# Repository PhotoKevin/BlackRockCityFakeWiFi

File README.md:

# BlackRockCityFakeWiFi

## Purpose
Create a joke WiFi access point for Black Rock City (aka Burning Man). The person trying to use the access point gets a huge list of Terms and Conditions in ever smaller font. Once they agree, they are run through some questions to "Prove they're not a robot".

Finally they get told that "Dorking around on the Internet" is against the principle of Immediacy and are dumped.

]
]
])

## Development Environment
I developed this on generic ESP8266 and ESP32 boards using the Arduino IDE. It also supports the OLED display on a Heltec WiFi Kit 32 (V3) or WiFi Kit 8. In addition to the OLED the Heltec boards are nice in that they can run off of either USB or a LiPo battery and can charge the battery from USB.

The web pages were created with the [Pulsar](https://pulsar-edit.dev) editor. A small C program is then used to convert the
pages into data stored in the main flash memory. The C program was developed in Visual Studio 2019.

Boards that I have tested on are:

- [Heltec WiFi Kit 32 (V3)](https://heltec.org/project/wifi-kit32-v3/)  
- [Heltec WiFi Kit 8](https://heltec.org/project/wifi-kit-8/)  
- [LOLIN (Wemos) D1 R1](https://www.wemos.cc/en/latest/d1/index.html)  
- [IdeaSpark ESP32](https://www.amazon.com/s?k=ideaspark)

## Captive Portal
The code implements a Captive Portal which operates like the typical free WiFi you'd find at a restaurant.
When the user connects it grabs all traffic from that user regardless of what they asked for and redirects it
to its signon process. I owe a lot to the [Mobile Rick Roll](https://github.com/idolpx/mobile-rr) project for their work in figuring out how to
implement this.

## Building the project
I'm using the Arduino 2.3.2 IDE.

- After installing the IDE go to the preferences (Control-Comma) and add these Additional Board Manager URLs.

- https://arduino.esp8266.com/stable/package_esp8266com_index.json  
- https://espressif.github.io/arduino-esp32/package_esp32_index.json
- https://github.com/Heltec-Aaron-Lee/WiFi_Kit_series/releases/download/3.0.0/package_heltec_esp32_index.json

- Exit and restart the IDE.

- In the Boards Manager (left column, second icon from the top) and install
    - "esp32 by Espressif Systems" version 3.0.1
    - "Arduino ESP32 Boards" version 2.0.13
    - "ESP8266 Boards" version 3.1.2

- Now go to the Library Manager (left column, third icon from the top) and install
    - ArduionJson by Benoit Blanchon. 7.0.4
    - ESP Async WebServer by me-no-dev 3.0.6
    - AsyncTCP by me-no-dev 3.1.4
    - ESPAsyncTCP by dvarrel 1.2.4
    - U8g2 by oliver. 2.34.22 - If using one of the boards with an OLED display.

- Plug your ESP board into a USB port.

- Click on the drop down in the button bar. Select your board and COM port.

- Lastly click on the Upload (right arrow) button to compile and install the software.

## Accessing the Status and Configuration Pages
- Bring up the list of access points and find BRC Open WiFi.
- Select that and you should be redirected to the giant page of legalese.
- Find the sentence "The following are representative examples only and do not comprise a comprehensive list of illegal</a> uses:"
- Click on the word "illegal".
- Log in with the default credentials of admin/changeme (both are all lower case).

]
]

## Configuration Options
- SSID - Name of the Access Point that shows up on your phone.
- Username - Username for accessing the statistics and settings.
- Password - Password for same. If left blank the previous password will remain in effect.
- IP Address - The IP Address for the Access Point. Note: Changing this affects the address used to access the configuration page.
- Netmask - The Netmask for the Access Point. You almost certainly should not change this.
- Master Device - The MAC address of a master device (aka your phone) that will be automatically logged in and sent to the status page.
- Current Device - The MAC address of the device you're currently using. Displayed so you can copy it into the Master Device if you want.

Changing the settings will cause the ESP to reboot.

# Modifying the HTML pages

The html directory contains all of the HTML, CSS, JavaScript, etc. It has to be converted into
a cpp file with strings. This can be done with the HtmlHelper program. You have to build the HtmlHelper with Visual Studio, or some other C compiler. Then run it as follows to put it into a C file

> HtmlHelper.exe --output=webpages.cpp --include=BMWiFi.h blocked.html brc.css checkbox.css legal.html question.html questions.js questions.json debugdata.js radio2.css banned.html banned.js redirect.html status.html status.js bmwifi.js settings.html settings.js login.html

Move the resulting webpages.cpp file over to the BMWiFi directory.
> move *.cpp ..\BMWiFi

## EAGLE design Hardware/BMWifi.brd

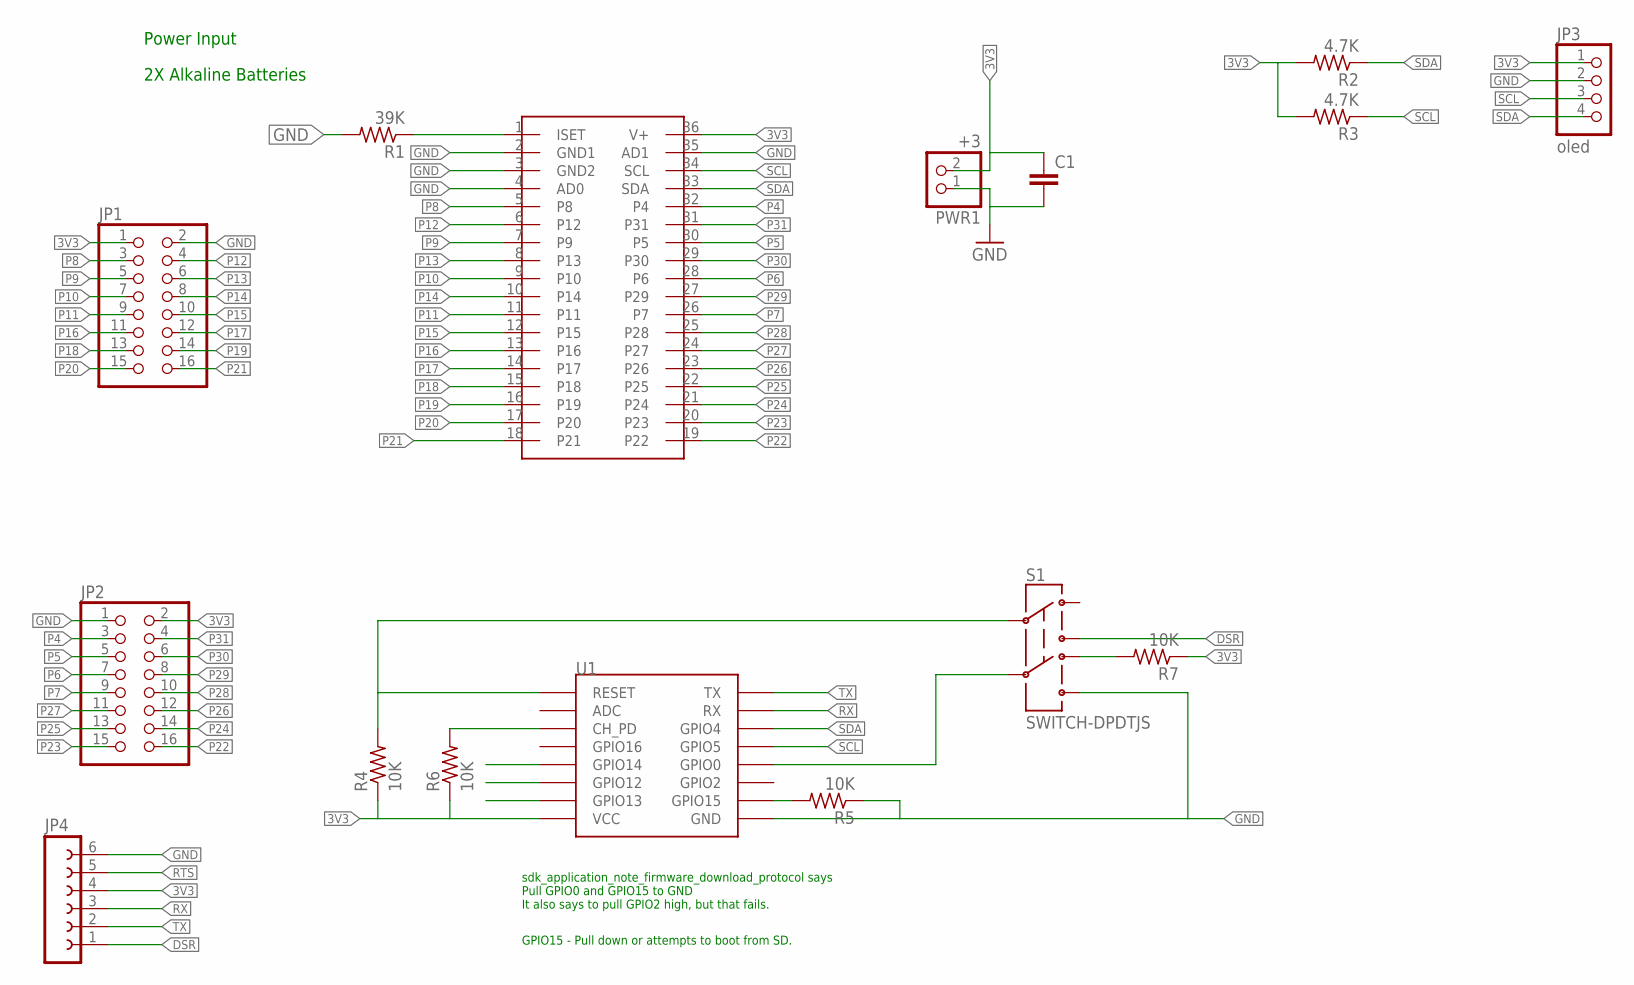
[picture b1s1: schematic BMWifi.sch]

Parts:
C1: C2.5/2; C2.5-2
JP1, JP2: PINHD-2X8; 2X08
JP3: oled; 1X04
JP4: FE06W
PWR1: +3; 1X02
R1: 39K; M1206
R2, R3: 4.7K; M1206
R4, R5, R6, R7: 10K; M1206
S1: SWITCH-DPDTJS; JS202011CQN
U1: ESP12
U$1: MAX6956; SSOP36

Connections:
3V3: C1.1, JP1.1, JP2.2, JP3.1, JP4.4, PWR1.2, R2.2, R3.2, R4.1, R6.1, R7.1, U1.VCC, U$1.36 (V+)
CH_PD: R6.2, U1.CH_PD
DSR: JP4.1, S1.3
GND: C1.2, JP1.2, JP2.1, JP3.2, JP4.6, PWR1.1, R1.2, R5.1, S1.6, U1.GND, U$1.2 (GND1), U$1.3 (GND2), U$1.4 (AD0), U$1.35 (AD1)
GPIO0: S1.5, U1.GPIO0
GPIO14: U1.GPIO14
GPIO15: R5.2, U1.GPIO15
ISET: R1.1, U$1.1 (ISET)
unnamed: R7.2, S1.4
P4: JP2.3, U$1.32 (P4)
P5: JP2.5, U$1.30 (P5)
P6: JP2.7, U$1.28 (P6)
P7: JP2.9, U$1.26 (P7)
P8: JP1.3, U$1.5 (P8)
P9: JP1.5, U$1.7 (P9)
P10: JP1.7, U$1.9 (P10)
P11: JP1.9, U$1.11
P12: JP1.4, U$1.6 (P12)
P13: JP1.6, U$1.8 (P13)
P14: JP1.8, U$1.10 (P14)
P15: JP1.10, U$1.12 (P15)
P16: JP1.11, U$1.13 (P16)
P17: JP1.12, U$1.14 (P17)
P18: JP1.13, U$1.15 (P18)
P19: JP1.14, U$1.16 (P19)
P20: JP1.15, U$1.17 (P20)
P21: JP1.16, U$1.18 (P21)
P22: JP2.16, U$1.19 (P22)
P23: JP2.15, U$1.20 (P23)
P24: JP2.14, U$1.21 (P24)
P25: JP2.13, U$1.22 (P25)
P26: JP2.12, U$1.23 (P26)
P27: JP2.11, U$1.24 (P27)
P28: JP2.10, U$1.25 (P28)
P29: JP2.8, U$1.27 (P29)
P30: JP2.6, U$1.29 (P30)
P31: JP2.4, U$1.31
RESET: R4.2, S1.2, U1.RESET
RTS: JP4.5
RX: JP4.3, U1.RX
SCL: JP3.3, R3.1, U1.GPIO5, U$1.34 (SCL)
SDA: JP3.4, R2.1, U1.GPIO4, U$1.33 (SDA)
TX: JP4.2, U1.TX

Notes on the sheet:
Power Input
2X Alkaline Batteries
GPIO15 - Pull down or attempts to boot from SD.
sdk_application_note_firmware_download_protocol says Pull GPIO0 and GPIO15 to GND It also says to pull GPIO2 high, but that fails.

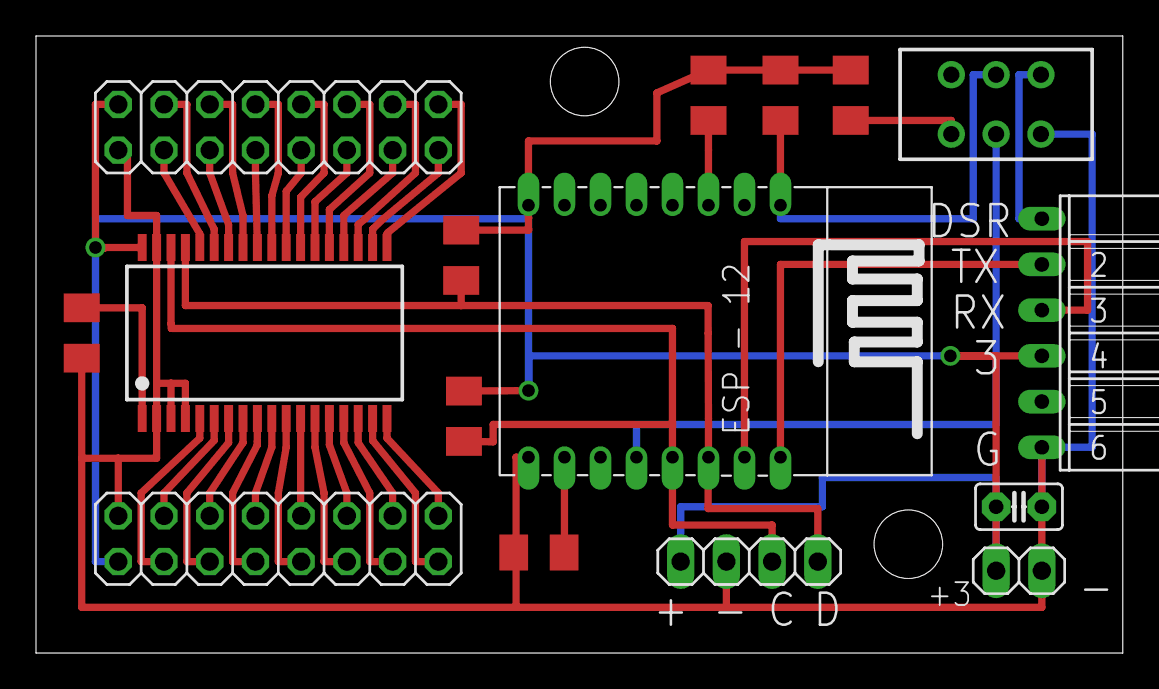
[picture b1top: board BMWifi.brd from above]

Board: 2 copper layers, 60.4 x 34.3 mm, 16 parts (0 on the bottom side), 41 nets.

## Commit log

2021-12-11 Initial proof of concept
2021-12-16 Convert to be AJAX. Most web functionality is in place.
2021-12-21 Fixed all of the html/css issues and have the pages looking decent.
2021-12-21 Ignore txt files.
2021-12-24 Major work on the banning logic
2021-12-24 Fixed eeprom save logic
2022-03-11 Update BMWifi.ino
    Turn off debug mode
2022-05-22 Don't use px in CSS. Use em'instead.
2022-05-22 Get the redirects for Android Captive Portal working. Set clock from client.
2022-05-23 Moved configurable things to Config.h
2022-05-24 Added a status screen
2022-05-26 Merge all web pages into a single cpp file
    Updated the HtmlHelper so it can merge all of the web pages into one file.
2022-05-26 Get working with Win 10
2022-06-01 Ensure the clock has been set before logging any time stamps
2022-06-02 Remove some status items
2022-06-02 Break out counts for Android vs Apple
2022-06-06 Make the setting of element text more bullet proof
    Make the setting of element text more bullet proof
2022-06-06 Display the voltage number
2022-06-06 Remove the hardware tree.
    I don't know why I thought I needed this when I started. Maybe an accident of copying from an old project.
2022-06-07 Start of support for online configuration.
2022-06-09 Started to add a way to configure at runtime
2022-06-24 Implemented configuration screens and user/password
2022-06-26 CSS and formatting error fix.
2022-06-30 Improved the debug messages a bit
2022-08-05 Change from ESP8266 to ESP32
    Converted from ESP8266 to ESP32 so I could get https. This involved an entire new set of API calls.
2022-08-11 Use a real cert for bmwifi.gt.org
    Ridley says this one worked with Android 12.
2022-08-11 Set title via AJAX, not a cookie
2022-08-22 Probably what I'll take to BRC.
    Still didn't work on Greg's Android 12 phone.
    Removed cookie.
    Added a login link
    Cleaned up a lot of logging
    Proper reboot on settings change.
2023-05-17 Fixed formatting
2023-06-03 When through a connection sequence correctly on my old phone.
2023-06-06 Ripped out https support. It was a mistake to add it.
2023-06-08 Fix punctuation
2023-06-08 Fixed name collision
2023-06-08 Changed to a different web server library that works on both ESP8266 and ESP32 chips.
2023-06-11 Cleaned up some tabs and indentation
2023-06-11 Added some padding in the bottom of the questions box.
2023-08-21 Cleaned up the legalize to make the text shrink more
2024-06-21 Updated Arduino to 2.3.2 and other libraries.
2024-06-21 Strip out Dhcp mistake
2024-06-21 Updated default pw
2024-06-22 Implemented changing the settings. Updated status and ReadMe
2024-06-22 Time display was wrong.
2024-06-22 Updated build instructions
2024-06-26 Use str_copy. Count unknown agents and save header for debug.
2024-07-04 Fix iPhone detection.
2024-07-04 Support IdeaSpark boards. Support U8G2 for no reason.
2024-07-05 Support the Heltec Wifi Kit 32 V3
2024-07-07 Removed support for old Heltec ESP32. Not supported by current libraries.
2024-07-07 Change Web Kit 32 references to say V3.
2024-07-08 Change to me-no-dev's webserver library. Add screenshots to README.md
2024-07-09 Have the defaults use the final octet of the mac.
    This change means you can make a bunch of access points and not have them colliding with each other.
2024-12-12 Fixed bug with timestamp. Added some logging. Beginnings of display timeout.

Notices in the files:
Hardware/BMWifi.brd:
(c) 2017 Kevin Nickerson
